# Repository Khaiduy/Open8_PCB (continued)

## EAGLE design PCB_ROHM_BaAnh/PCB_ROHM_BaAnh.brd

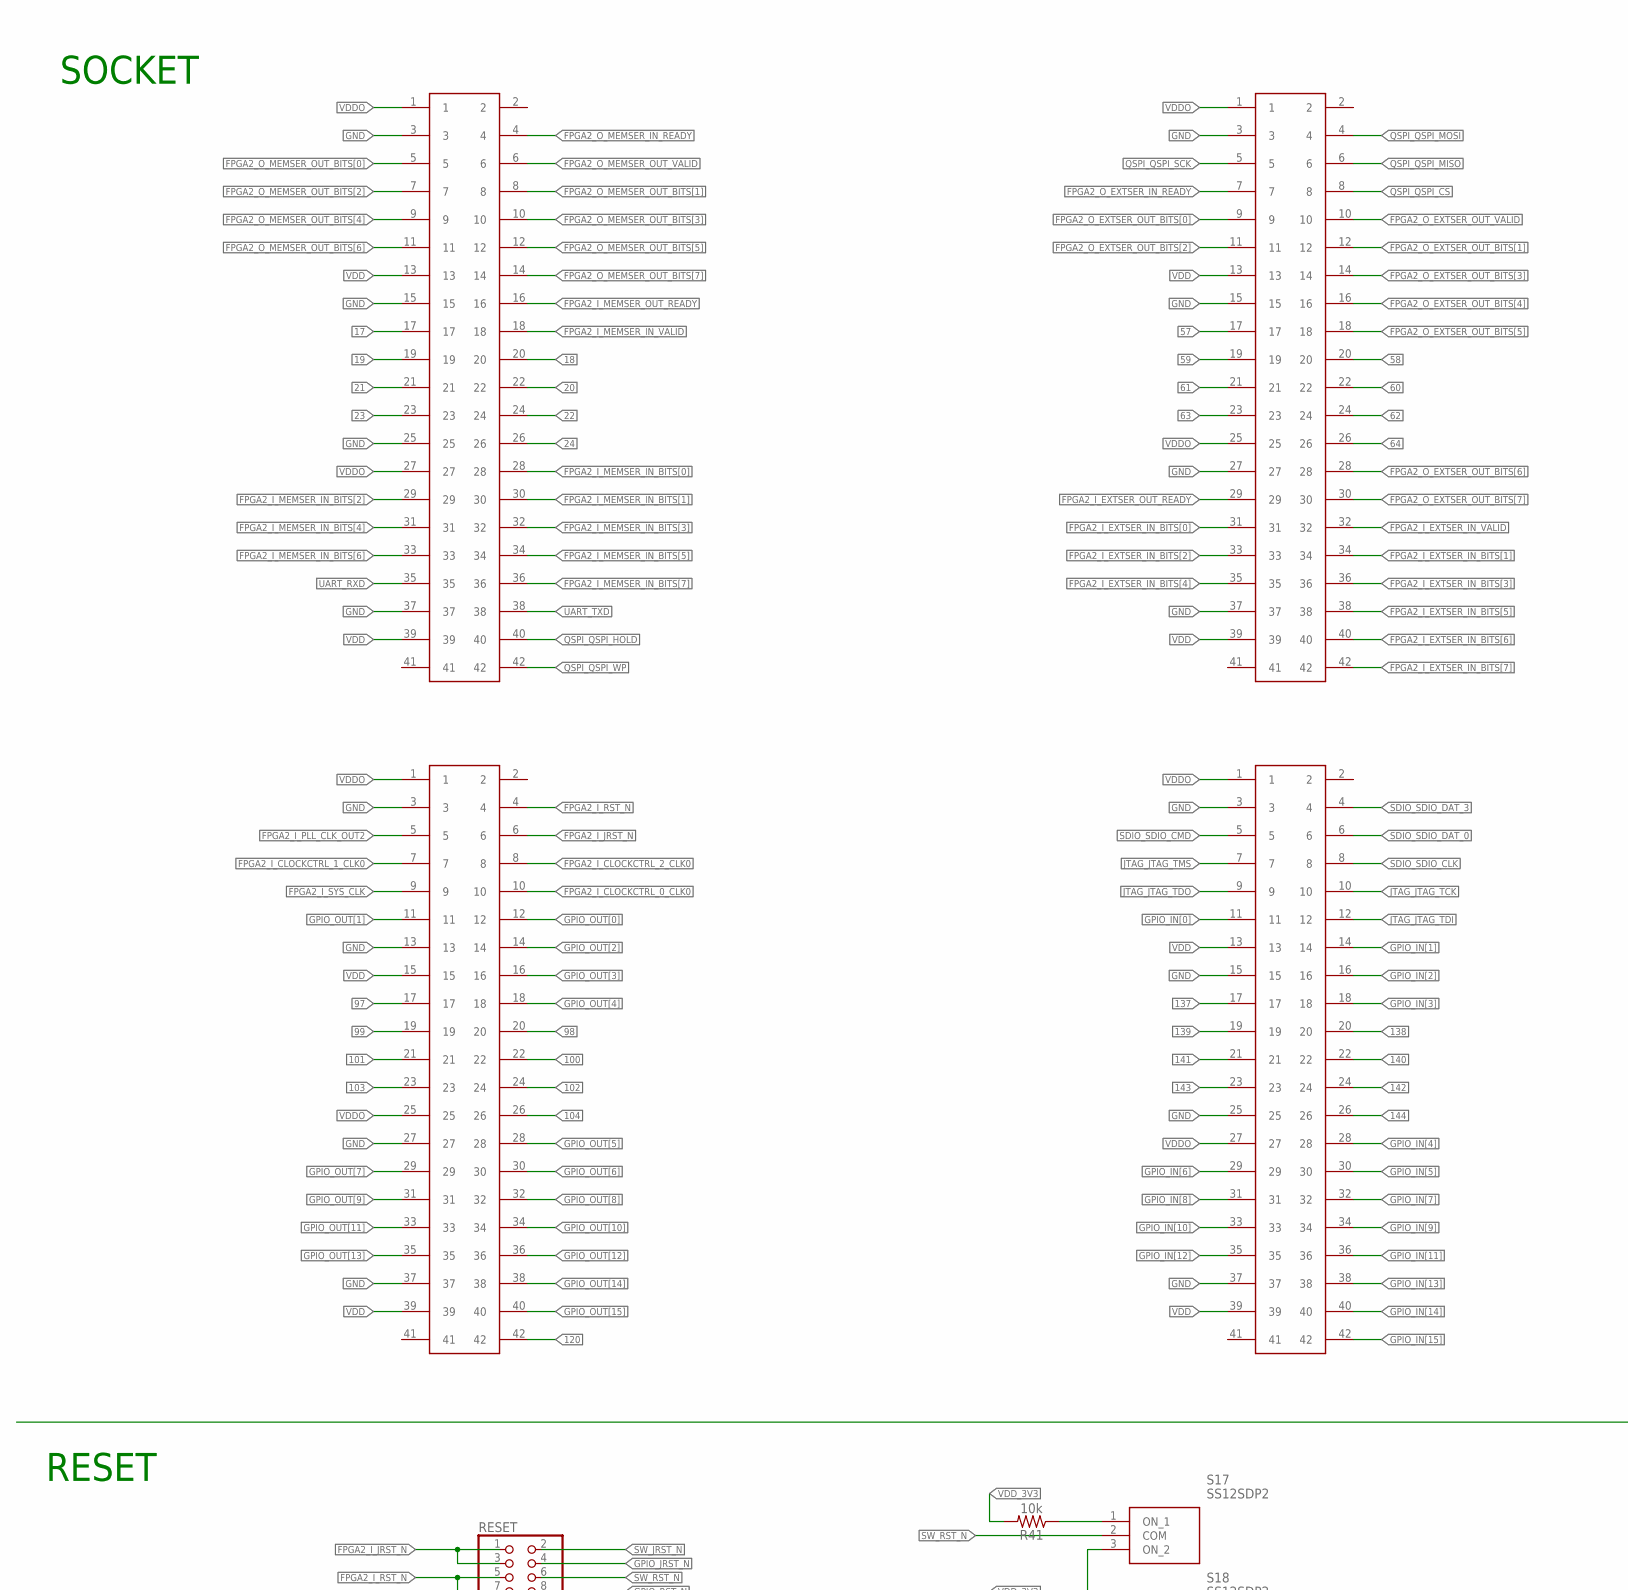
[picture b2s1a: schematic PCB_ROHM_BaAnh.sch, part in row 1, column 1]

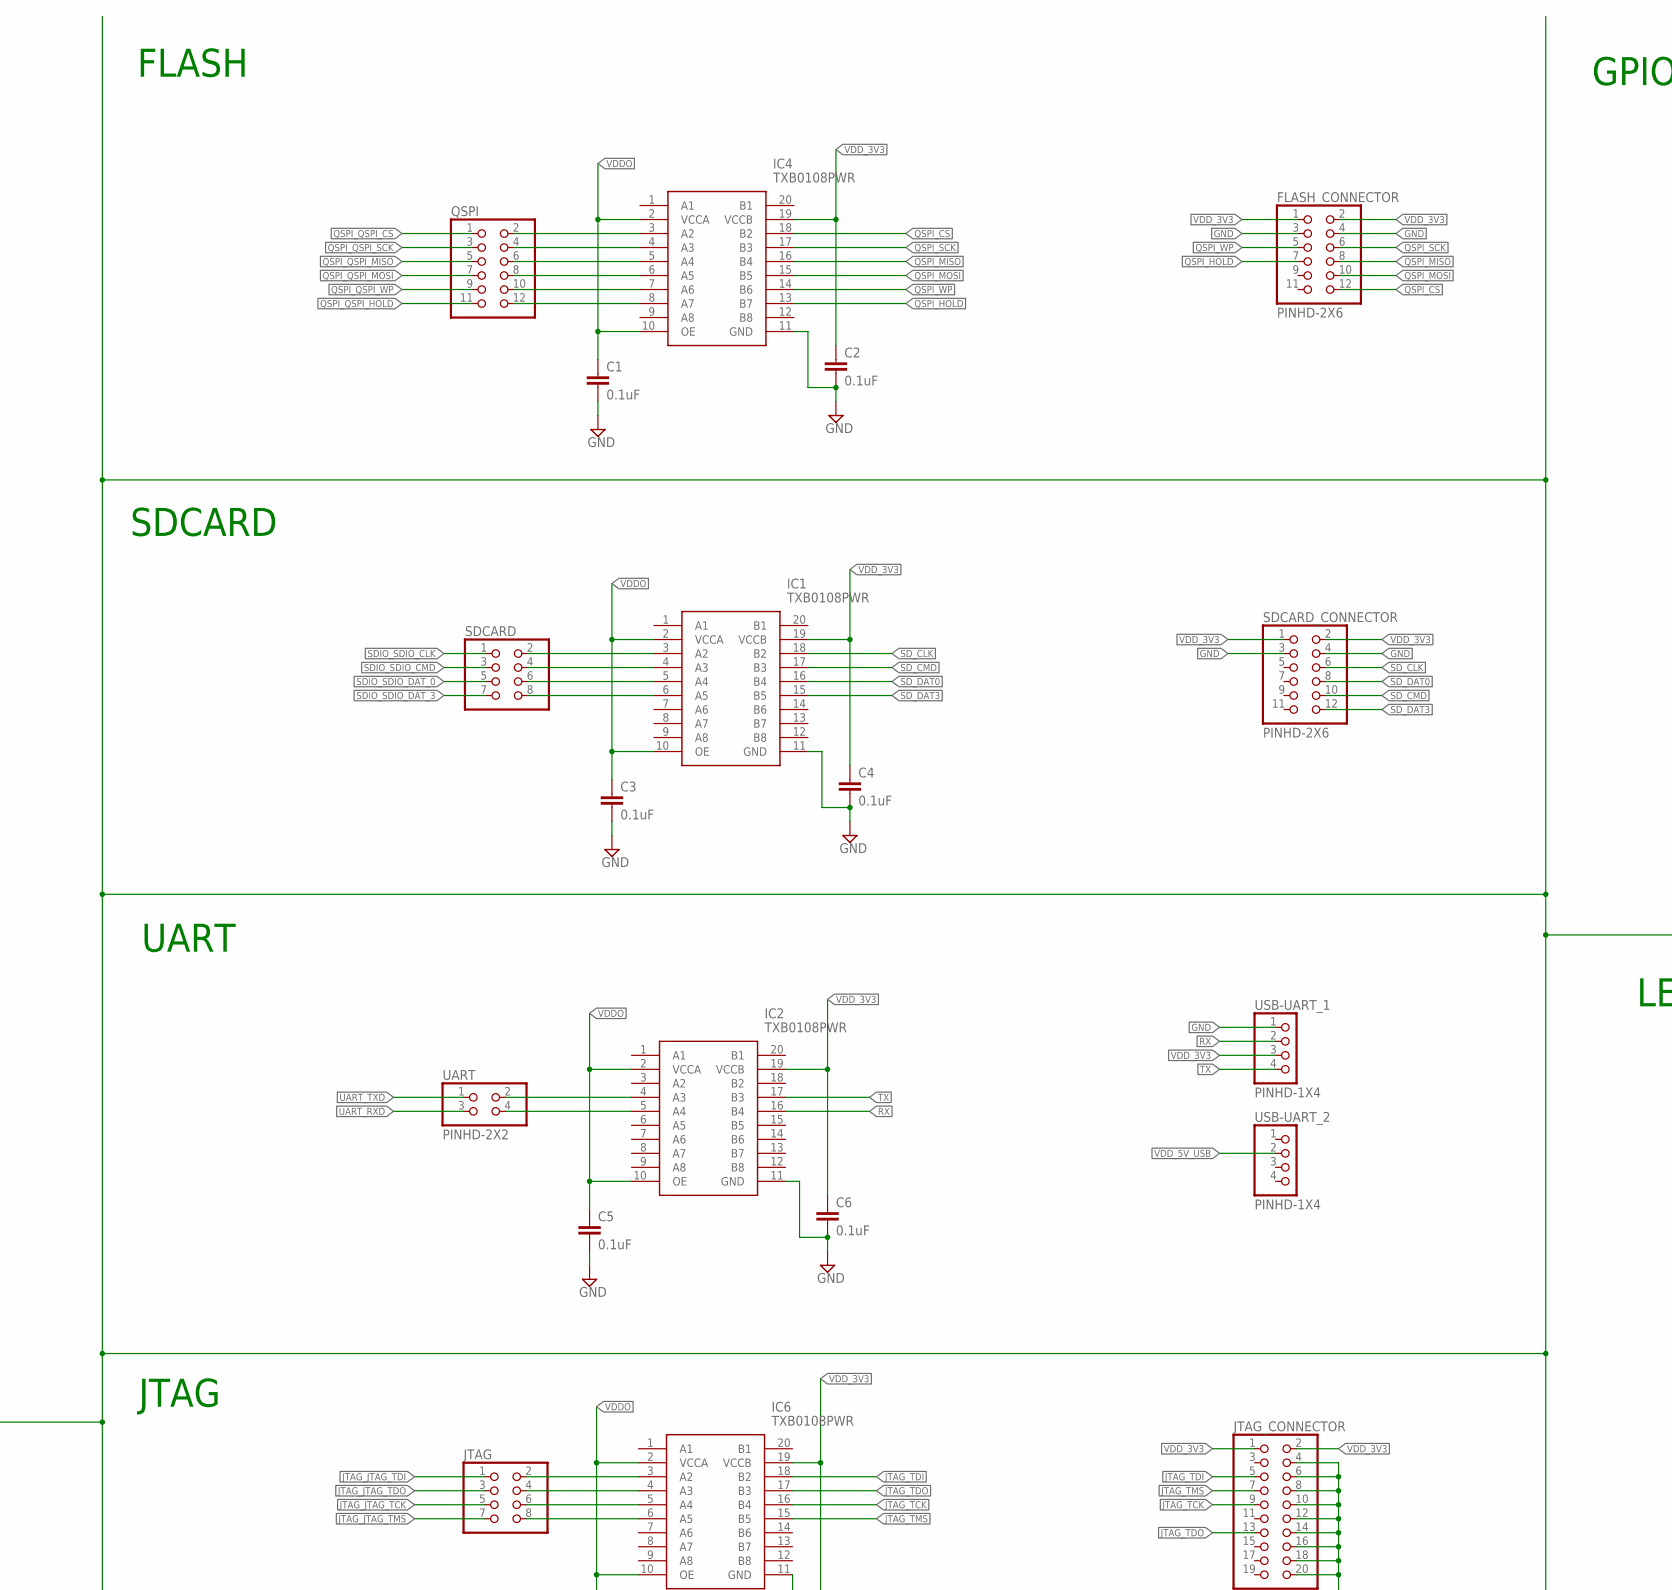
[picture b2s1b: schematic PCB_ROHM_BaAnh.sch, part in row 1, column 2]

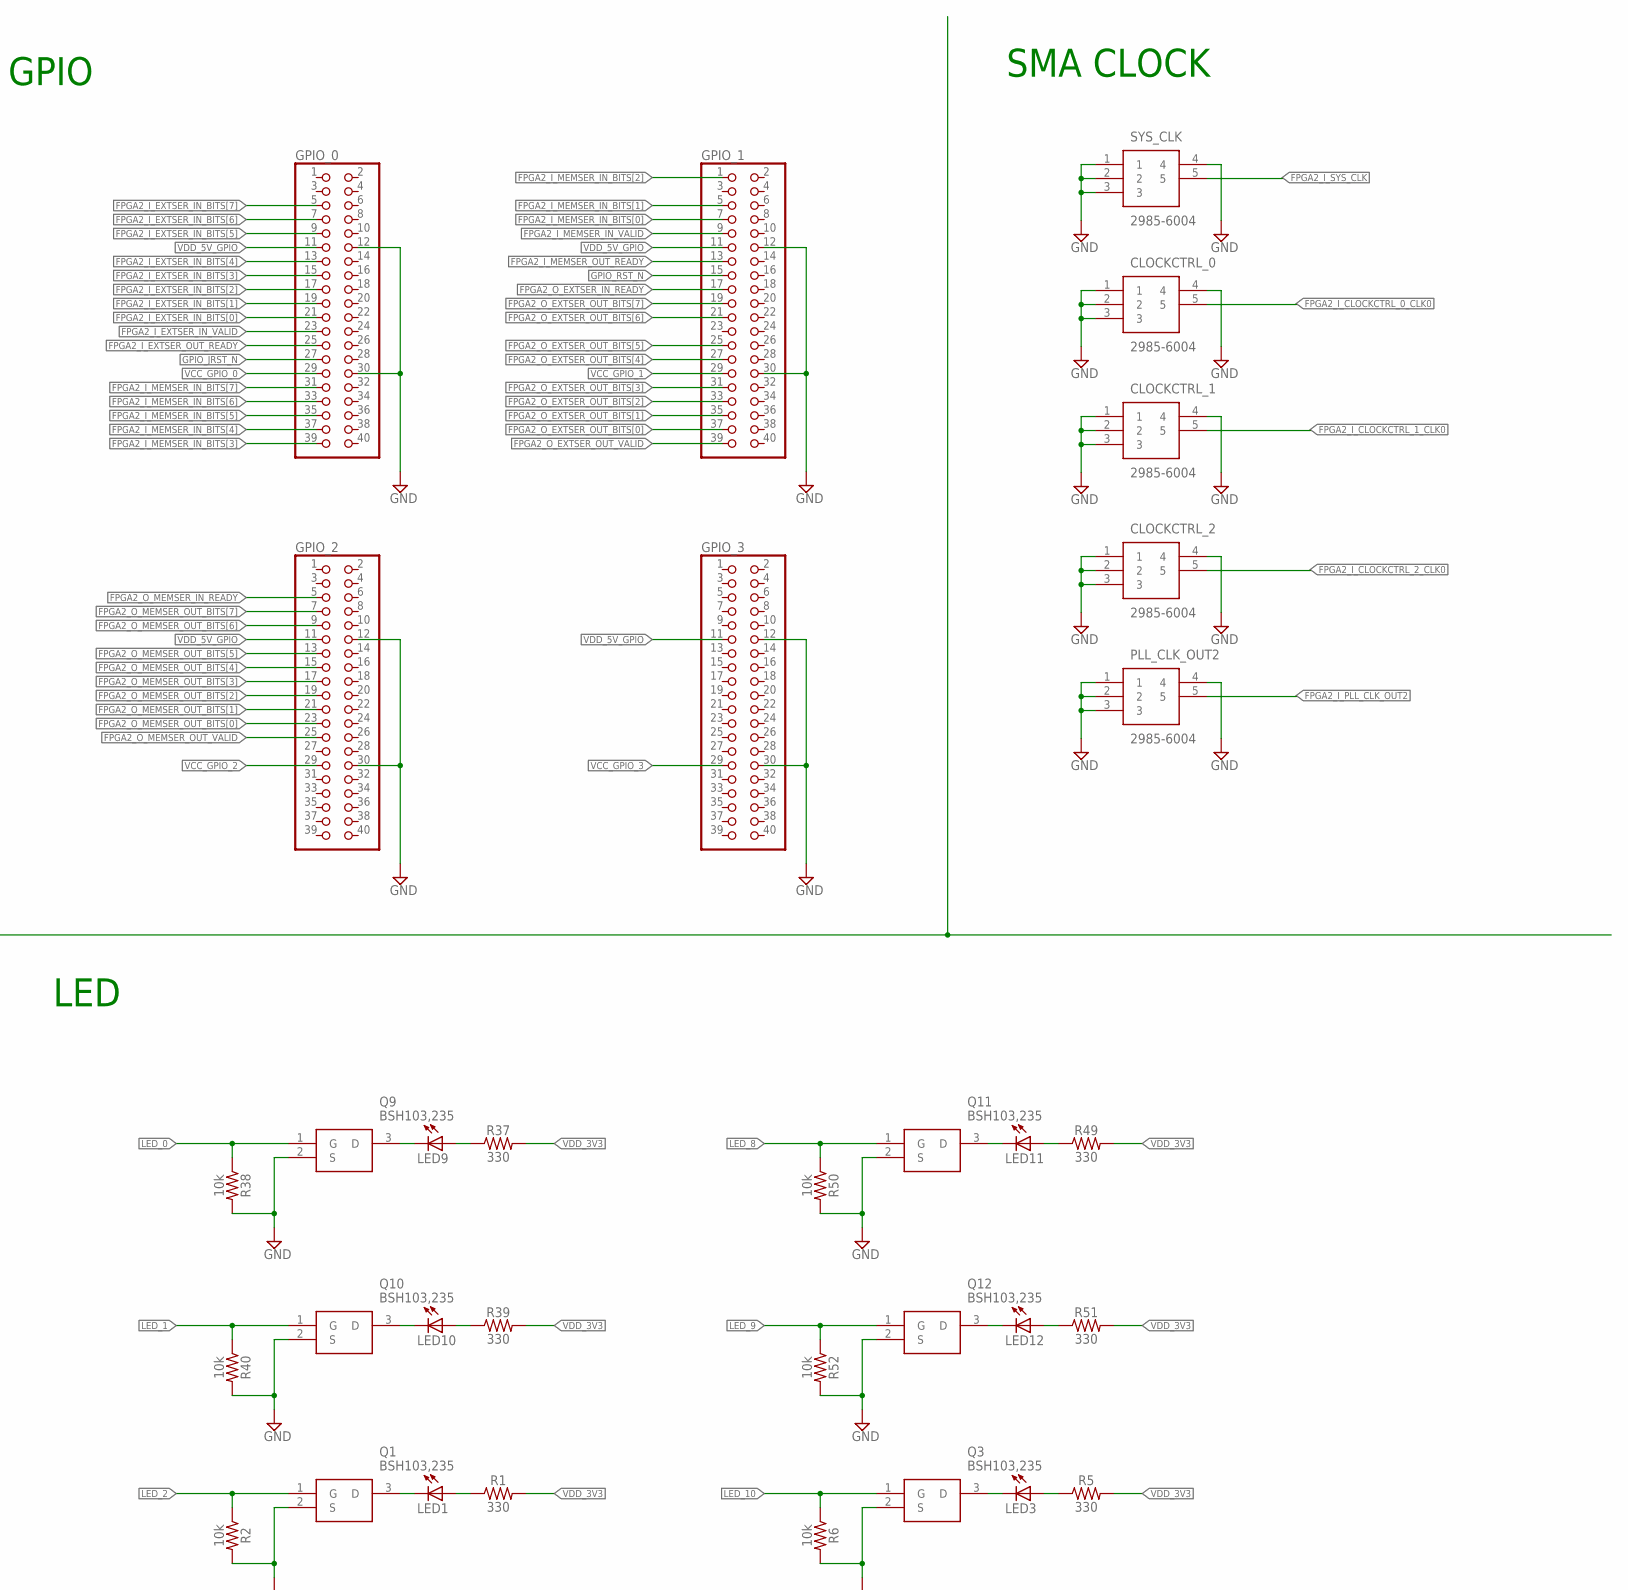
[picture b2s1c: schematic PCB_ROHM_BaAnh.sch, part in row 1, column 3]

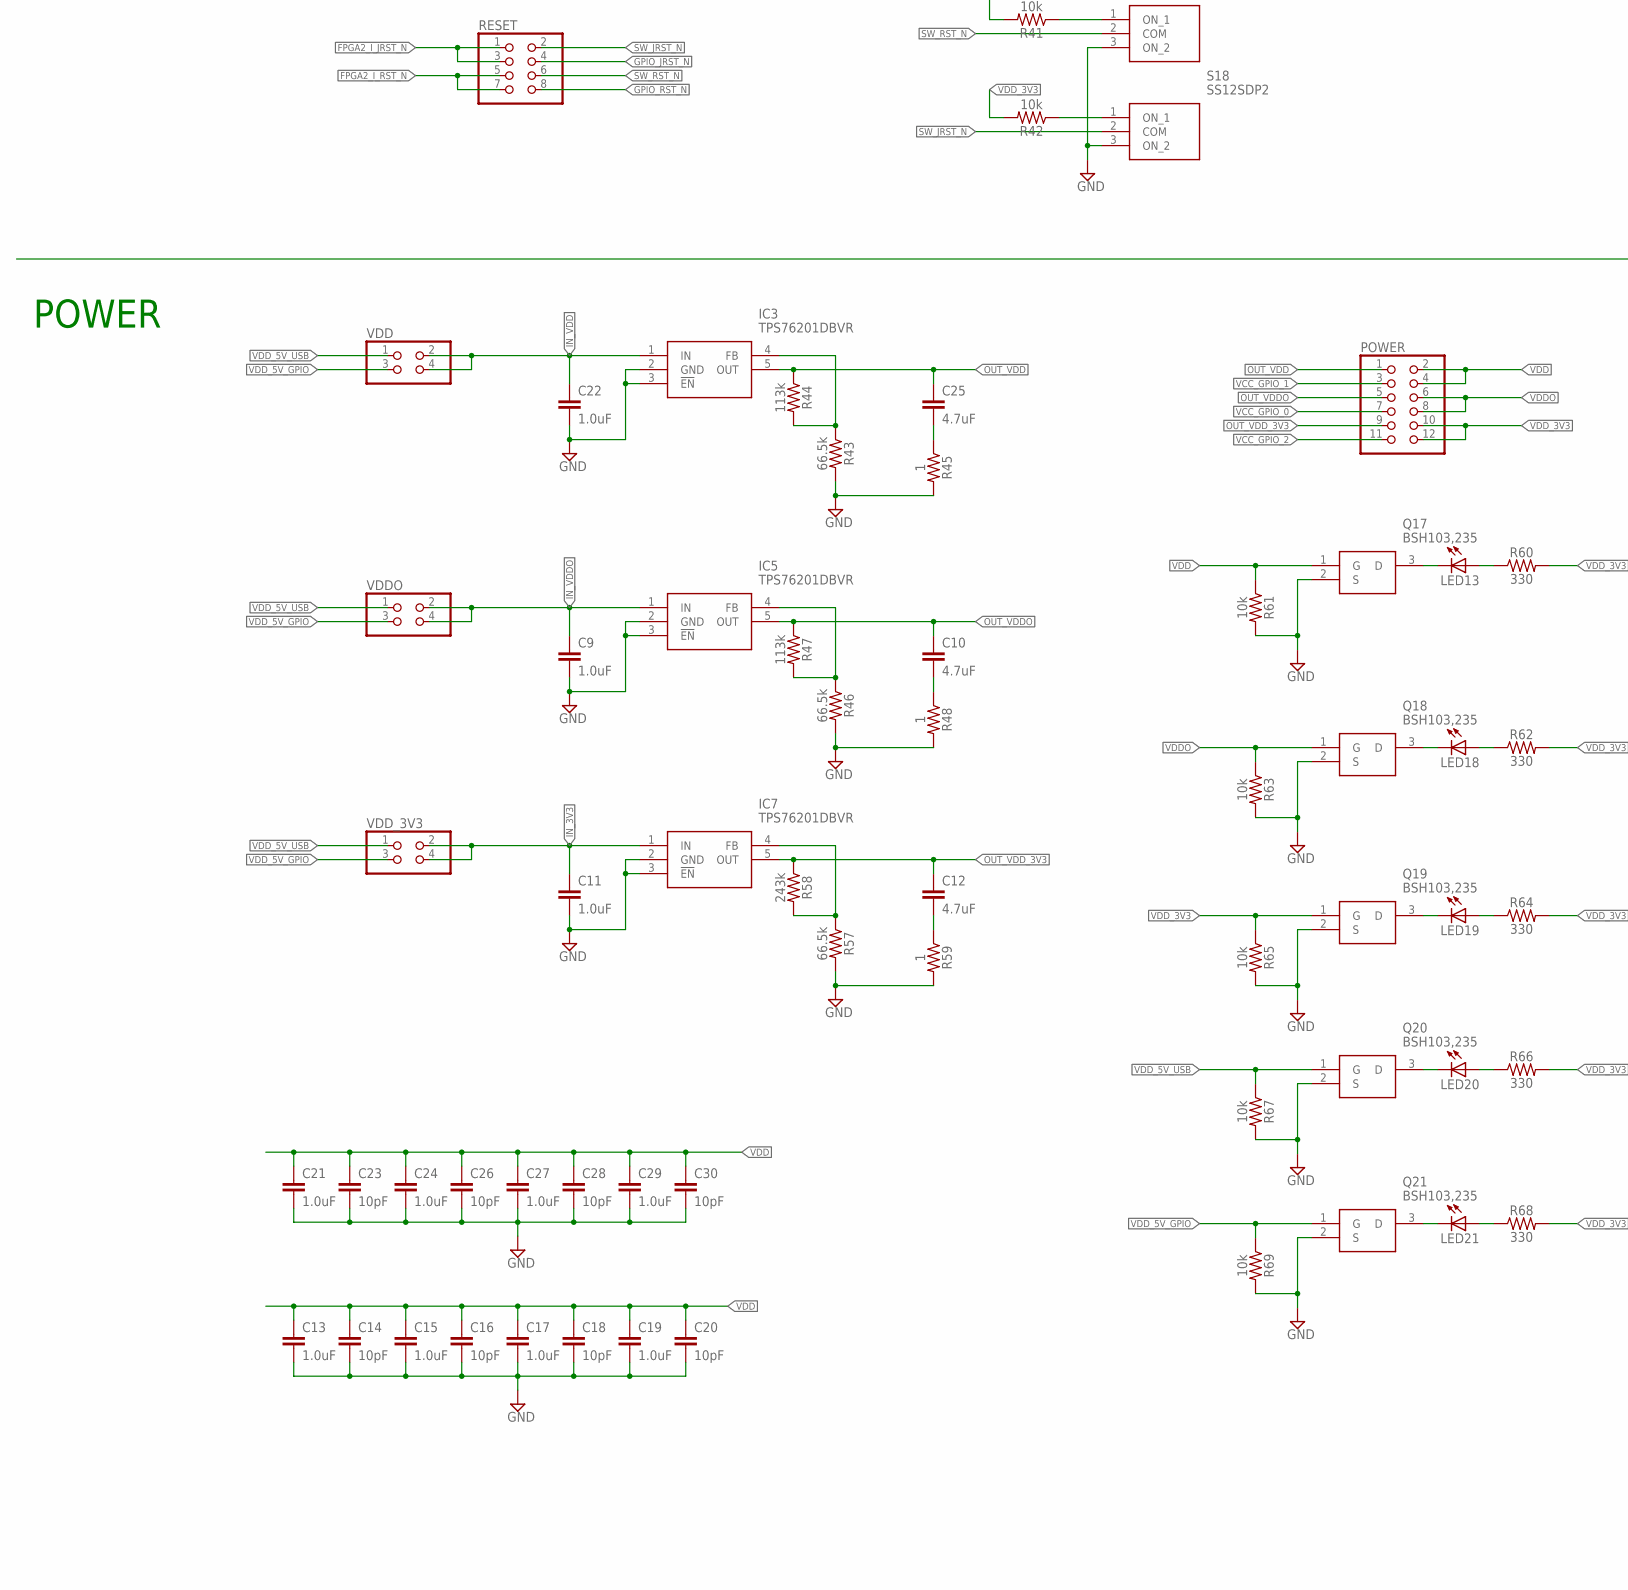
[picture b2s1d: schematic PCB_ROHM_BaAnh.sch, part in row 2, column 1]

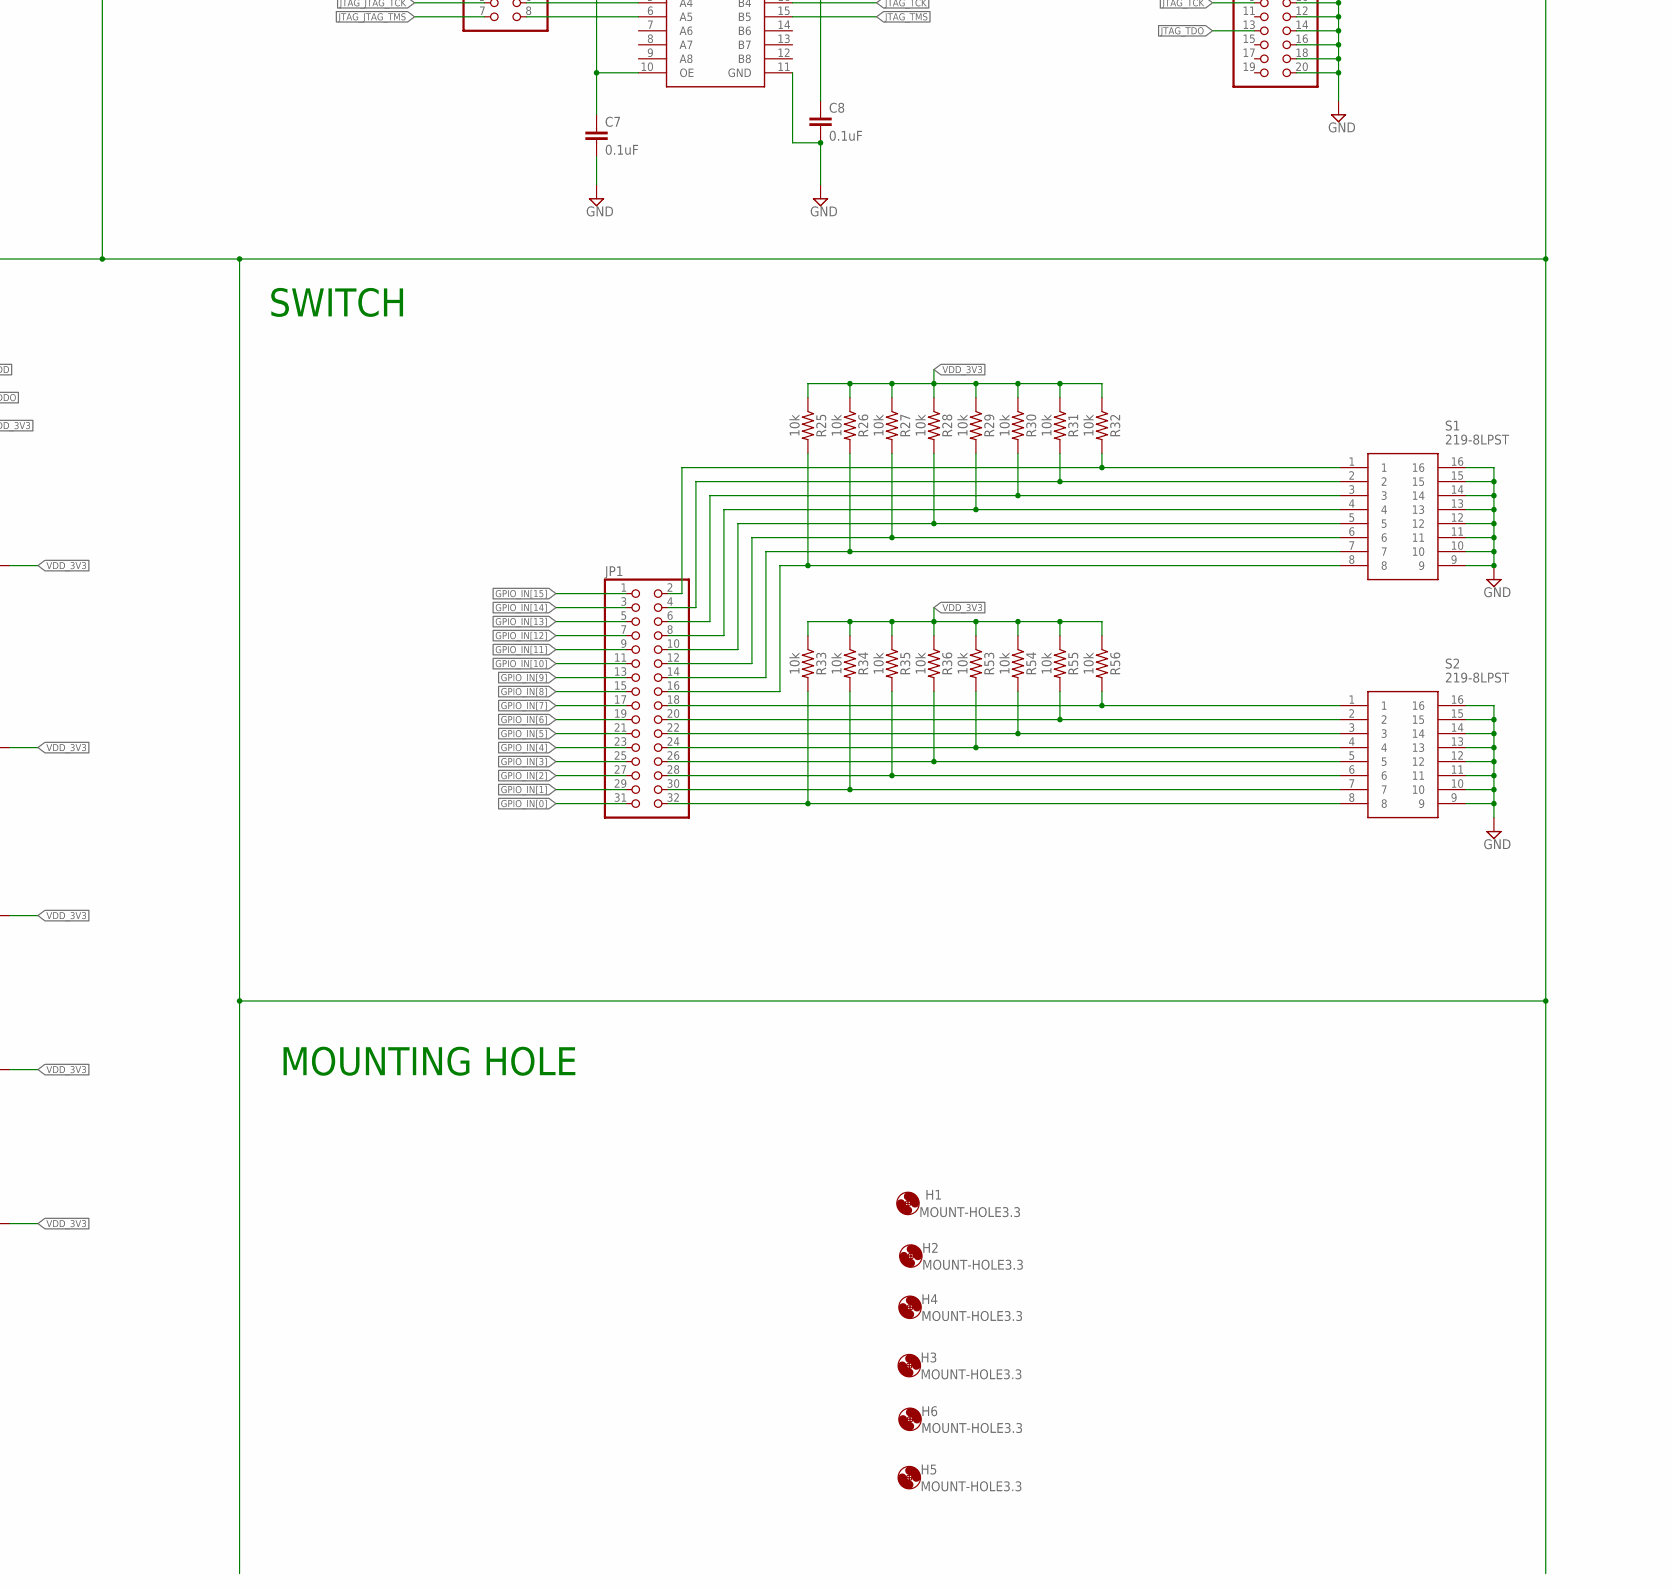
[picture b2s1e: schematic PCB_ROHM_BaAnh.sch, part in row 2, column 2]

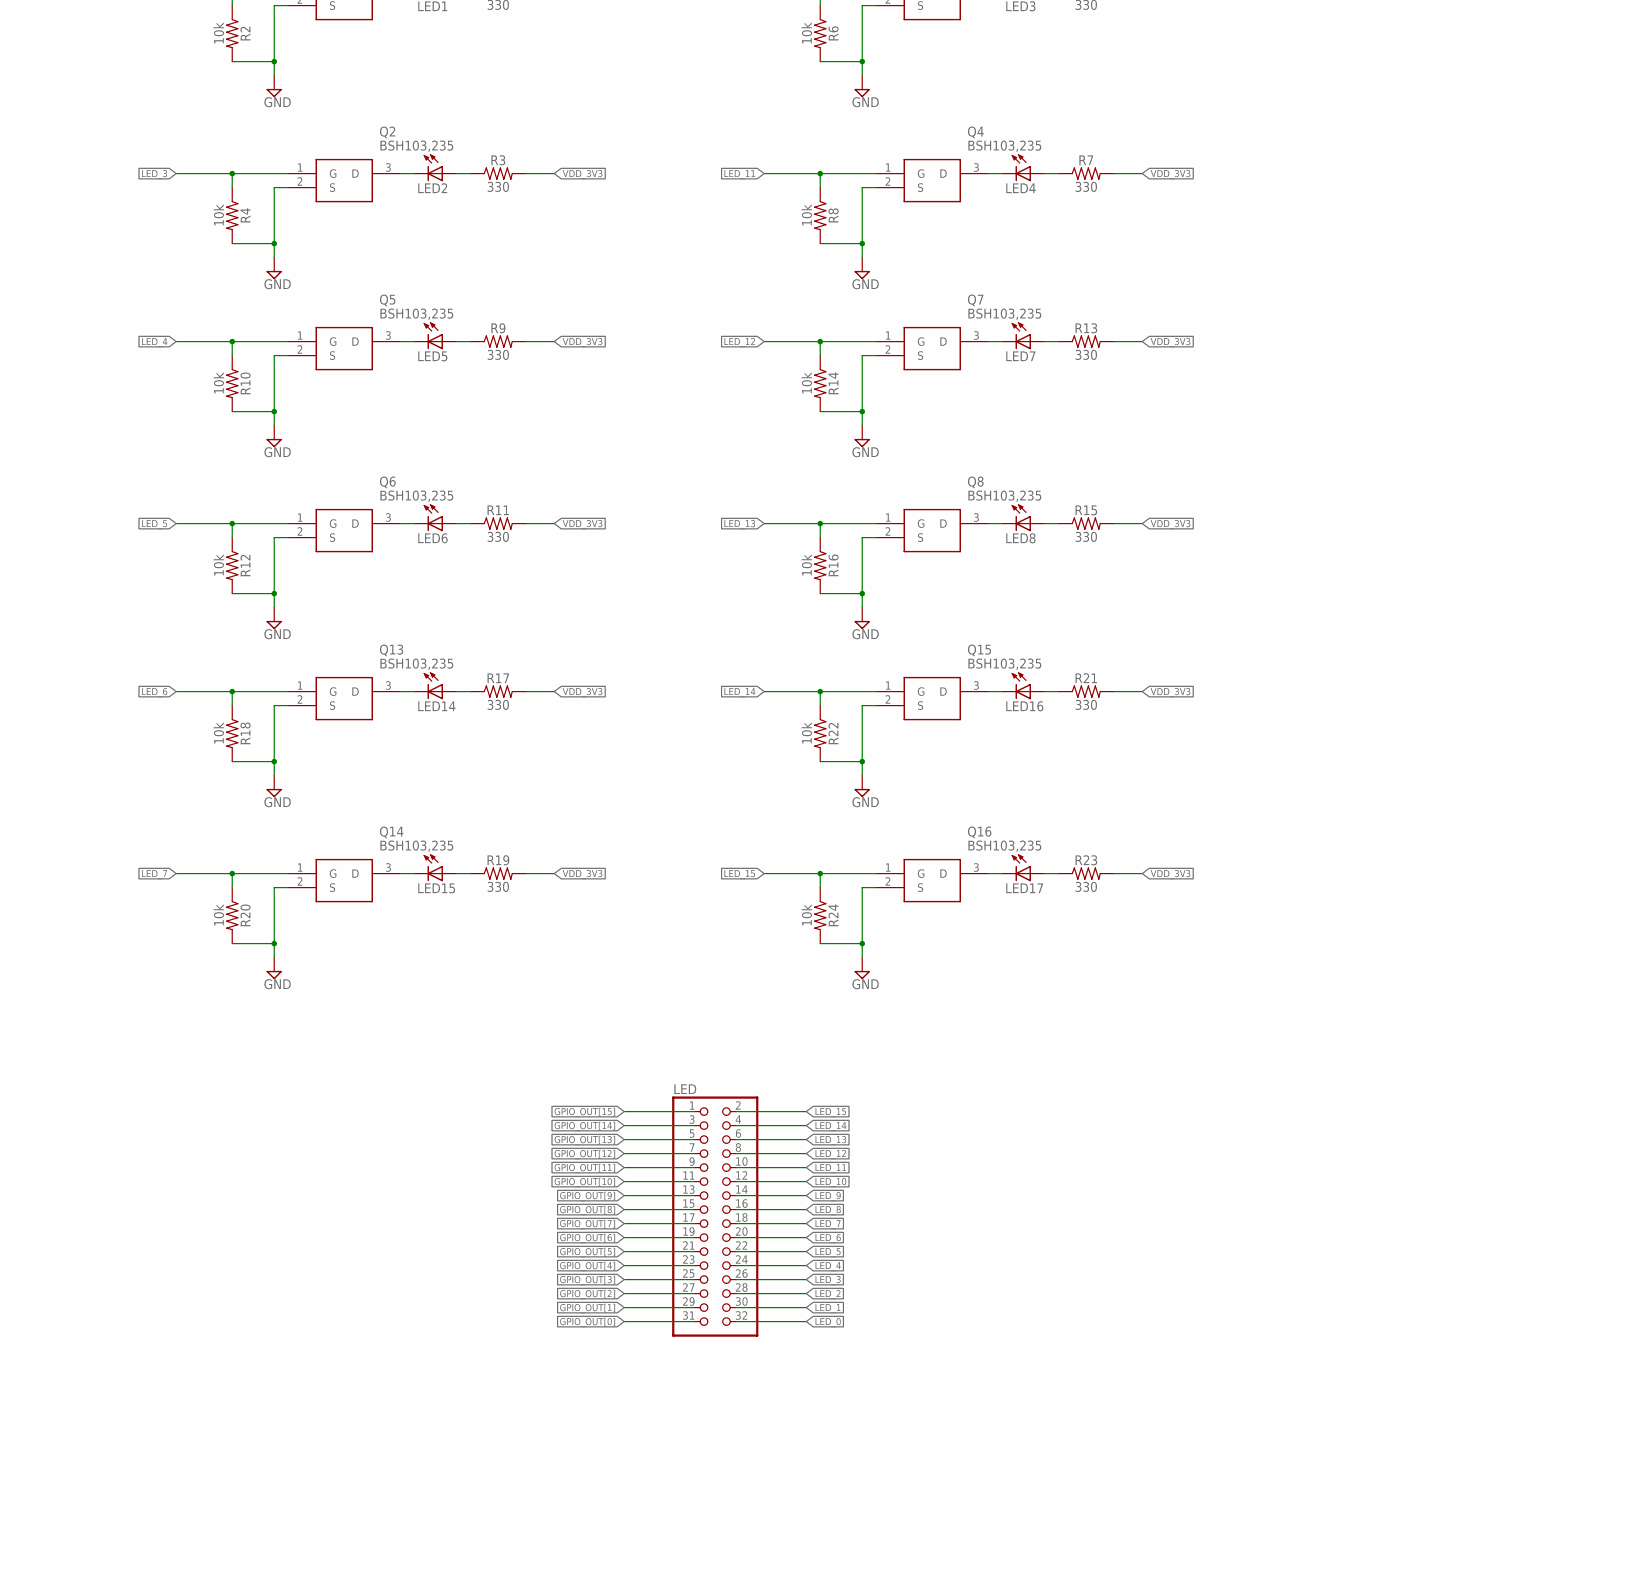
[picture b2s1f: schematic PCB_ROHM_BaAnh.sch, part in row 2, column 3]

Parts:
C1, C2, C3, C4, C5, C6, C7, C8: 0.1uF; 0805
C9, C11, C13, C15, C17, C19, C21, C22, C24, C27, C29: 1.0uF; 0805
C10, C12, C25: 4.7uF; 0805
C14, C16, C18, C20, C23, C26, C28, C30: 10pF; 0805
CLOCKCTRL_0, CLOCKCTRL_1, CLOCKCTRL_2: 2985-6004; 29856004
FLASH_CONNECTOR: PINHD-2X6; 2X06
GPIO_0, GPIO_1, GPIO_2, GPIO_3: PINHD-2X20; 2X20
H1, H2, H3, H4, H5, H6: MOUNT-HOLE3.3; 3,3
IC1, IC2, IC4, IC6: TXB0108PWR; SOP65P640X120-20N
IC3, IC5, IC7: TPS76201DBVR; SOT95P280X145-5N
JP1: PINHD-2X16; 2X16
JTAG: PINHD-2X4; 2X04
JTAG_CONNECTOR: PINHD-2X10; 2X10
LED: PINHD-2X16; 2X16
LED1, LED2, LED3, LED4, LED5, LED6, LED7, LED8, LED9, LED10, LED11, LED12, LED13, LED14, LED15, LED16, LED17, LED18, LED19, LED20, LED21: LEDCHIP-LED0805; CHIP-LED0805
PLL_CLK_OUT2: 2985-6004; 29856004
POWER: PINHD-2X6; 2X06
Q1, Q2, Q3, Q4, Q5, Q6, Q7, Q8, Q9, Q10, Q11, Q12, Q13, Q14, Q15, Q16, Q17, Q18, Q19, Q20, Q21: BSH103,235; SOT95P230X110-3N
QSPI: PINHD-2X6; 2X06
R1, R3, R5, R7, R9, R11, R13, R15, R17, R19, R21, R23, R37, R39, R49, R51, R60, R62, R64, R66, R68: 330; 0805
R2, R4, R6, R8, R10, R12, R14, R16, R18, R20, R22, R24, R25, R26, R27, R28, R29, R30, R31, R32, R33, R34, R35, R36, R38, R40, R41, R42, R50, R52, R53, R54, R55, R56, R61, R63, R65, R67, R69: 10k; 0805
R43, R46, R57: 66.5k; 0805
R44, R47: 113k; 0805
R45, R48, R59: 1; 0805
R58: 243k; 0805
RESET: PINHD-2X4; 2X04
S1, S2: 219-8LPST; 2198LPST
S17, S18: SS12SDP2
SDCARD: PINHD-2X4; 2X04
SDCARD_CONNECTOR: PINHD-2X6; 2X06
SYS_CLK: 2985-6004; 29856004
U$1, U$2, U$3, U$4: 2X41_HEADER
UART: PINHD-2X2; 2X02
USB-UART_1, USB-UART_2: PINHD-1X4; 1X04
VDD: PINHD-2X2; 2X02
VDDO: PINHD-2X2; 2X02
VDD_3V3: PINHD-2X2; 2X02

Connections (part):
17: U$1.17
18: U$1.20
19: U$1.19
20: U$1.22
21: U$1.21
22: U$1.24
23: U$1.23
24: U$1.26
57: U$2.17
58: U$2.20
59: U$2.19
60: U$2.22
61: U$2.21
62: U$2.24
63: U$2.23
64: U$2.26
97: U$3.17
98: U$3.20
99: U$3.19
100: U$3.22
101: U$3.21
102: U$3.24
103: U$3.23
104: U$3.26
120: U$3.42
137: U$4.17
138: U$4.20
139: U$4.19
140: U$4.22
141: U$4.21
142: U$4.24
143: U$4.23
144: U$4.26
FPGA2_I_CLOCKCTRL_0_CLK0: CLOCKCTRL_0.5, U$3.10
FPGA2_I_CLOCKCTRL_1_CLK0: CLOCKCTRL_1.5, U$3.7
FPGA2_I_CLOCKCTRL_2_CLK0: CLOCKCTRL_2.5, U$3.8
FPGA2_I_EXTSER_IN_BITS[0]: GPIO_0.21, U$2.31
FPGA2_I_EXTSER_IN_BITS[1]: GPIO_0.19, U$2.34
FPGA2_I_EXTSER_IN_BITS[2]: GPIO_0.17, U$2.33
FPGA2_I_EXTSER_IN_BITS[3]: GPIO_0.15, U$2.36
FPGA2_I_EXTSER_IN_BITS[4]: GPIO_0.13, U$2.35
FPGA2_I_EXTSER_IN_BITS[5]: GPIO_0.9, U$2.38
FPGA2_I_EXTSER_IN_BITS[6]: GPIO_0.7, U$2.40
FPGA2_I_EXTSER_IN_BITS[7]: GPIO_0.5, U$2.42
FPGA2_I_EXTSER_IN_VALID: GPIO_0.23, U$2.32
FPGA2_I_EXTSER_OUT_READY: GPIO_0.25, U$2.29
FPGA2_I_JRST_N: RESET.1, RESET.3, U$3.6
FPGA2_I_MEMSER_IN_BITS[0]: GPIO_1.7, U$1.28
FPGA2_I_MEMSER_IN_BITS[1]: GPIO_1.5, U$1.30
FPGA2_I_MEMSER_IN_BITS[2]: GPIO_1.1, U$1.29
FPGA2_I_MEMSER_IN_BITS[3]: GPIO_0.39, U$1.32
FPGA2_I_MEMSER_IN_BITS[4]: GPIO_0.37, U$1.31
FPGA2_I_MEMSER_IN_BITS[5]: GPIO_0.35, U$1.34
FPGA2_I_MEMSER_IN_BITS[6]: GPIO_0.33, U$1.33
FPGA2_I_MEMSER_IN_BITS[7]: GPIO_0.31, U$1.36
FPGA2_I_MEMSER_IN_VALID: GPIO_1.9, U$1.18
FPGA2_I_MEMSER_OUT_READY: GPIO_1.13, U$1.16
FPGA2_I_PLL_CLK_OUT2: PLL_CLK_OUT2.5, U$3.5
FPGA2_I_RST_N: RESET.5, RESET.7, U$3.4
FPGA2_I_SYS_CLK: SYS_CLK.5, U$3.9
FPGA2_O_EXTSER_IN_READY: GPIO_1.17, U$2.7
FPGA2_O_EXTSER_OUT_BITS[0]: GPIO_1.37, U$2.9
FPGA2_O_EXTSER_OUT_BITS[1]: GPIO_1.35, U$2.12
FPGA2_O_EXTSER_OUT_BITS[2]: GPIO_1.33, U$2.11
FPGA2_O_EXTSER_OUT_BITS[3]: GPIO_1.31, U$2.14
FPGA2_O_EXTSER_OUT_BITS[4]: GPIO_1.27, U$2.16
FPGA2_O_EXTSER_OUT_BITS[5]: GPIO_1.25, U$2.18
FPGA2_O_EXTSER_OUT_BITS[6]: GPIO_1.21, U$2.28
FPGA2_O_EXTSER_OUT_BITS[7]: GPIO_1.19, U$2.30
FPGA2_O_EXTSER_OUT_VALID: GPIO_1.39, U$2.10
FPGA2_O_MEMSER_IN_READY: GPIO_2.5, U$1.4
FPGA2_O_MEMSER_OUT_BITS[0]: GPIO_2.23, U$1.5
FPGA2_O_MEMSER_OUT_BITS[1]: GPIO_2.21, U$1.8
FPGA2_O_MEMSER_OUT_BITS[2]: GPIO_2.19, U$1.7
FPGA2_O_MEMSER_OUT_BITS[3]: GPIO_2.17, U$1.10
FPGA2_O_MEMSER_OUT_BITS[4]: GPIO_2.15, U$1.9
FPGA2_O_MEMSER_OUT_BITS[5]: GPIO_2.13, U$1.12
FPGA2_O_MEMSER_OUT_BITS[6]: GPIO_2.9, U$1.11
FPGA2_O_MEMSER_OUT_BITS[7]: GPIO_2.7, U$1.14
FPGA2_O_MEMSER_OUT_VALID: GPIO_2.25, U$1.6
GND: C1.2, C2.2, C3.2, C4.2, C5.2, C6.2, C7.2, C8.2, C9.2, C11.2, C13.2, C14.2, C15.2, C16.2, C17.2, C18.2, C19.2, C20.2, C21.2, C22.2, C23.2, C24.2, C26.2, C27.2, C28.2, C29.2, C30.2, CLOCKCTRL_0.1, CLOCKCTRL_0.2, CLOCKCTRL_0.3, CLOCKCTRL_0.4, CLOCKCTRL_1.1, CLOCKCTRL_1.2, CLOCKCTRL_1.3, CLOCKCTRL_1.4, CLOCKCTRL_2.1, CLOCKCTRL_2.2, CLOCKCTRL_2.3, CLOCKCTRL_2.4, FLASH_CONNECTOR.3, FLASH_CONNECTOR.4, GPIO_0.12, GPIO_0.30, GPIO_1.12, GPIO_1.30, GPIO_2.12, GPIO_2.30, GPIO_3.12, GPIO_3.30, IC1.11 (GND), IC2.11 (GND), IC3.2 (GND), IC3.3 (!EN), IC4.11 (GND), IC5.2 (GND), IC5.3 (!EN), IC6.11 (GND), IC7.2 (GND), IC7.3 (!EN), JTAG_CONNECTOR.4, JTAG_CONNECTOR.6, JTAG_CONNECTOR.8, JTAG_CONNECTOR.10, JTAG_CONNECTOR.12, JTAG_CONNECTOR.14, JTAG_CONNECTOR.16, JTAG_CONNECTOR.18, JTAG_CONNECTOR.20, PLL_CLK_OUT2.1, PLL_CLK_OUT2.2, PLL_CLK_OUT2.3, PLL_CLK_OUT2.4, Q1.2 (S), Q2.2 (S), Q3.2 (S), Q4.2 (S), Q5.2 (S), Q6.2 (S), Q7.2 (S), Q8.2 (S)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
GPIO_IN[0]: JP1.31, U$4.11
GPIO_IN[1]: JP1.29, U$4.14
GPIO_IN[2]: JP1.27, U$4.16
GPIO_IN[3]: JP1.25, U$4.18
GPIO_IN[4]: JP1.23, U$4.28
GPIO_IN[5]: JP1.21, U$4.30
GPIO_IN[6]: JP1.19, U$4.29
GPIO_IN[7]: JP1.17, U$4.32
GPIO_IN[8]: JP1.15, U$4.31
GPIO_IN[9]: JP1.13, U$4.34
GPIO_IN[10]: JP1.11, U$4.33
GPIO_IN[11]: JP1.9, U$4.36
GPIO_IN[12]: JP1.7, U$4.35
GPIO_IN[13]: JP1.5, U$4.38
GPIO_IN[14]: JP1.3, U$4.40
GPIO_IN[15]: JP1.1, U$4.42
GPIO_JRST_N: GPIO_0.27, RESET.4
GPIO_OUT[0]: LED.31, U$3.12
GPIO_OUT[1]: LED.29, U$3.11
GPIO_OUT[2]: LED.27, U$3.14
GPIO_OUT[3]: LED.25, U$3.16
GPIO_OUT[4]: LED.23, U$3.18
GPIO_OUT[5]: LED.21, U$3.28
GPIO_OUT[6]: LED.19, U$3.30
GPIO_OUT[7]: LED.17, U$3.29
GPIO_OUT[8]: LED.15, U$3.32
GPIO_OUT[9]: LED.13, U$3.31
GPIO_OUT[10]: LED.11, U$3.34
GPIO_OUT[11]: LED.9, U$3.33
GPIO_OUT[12]: LED.7, U$3.36
GPIO_OUT[13]: LED.5, U$3.35
GPIO_OUT[14]: LED.3, U$3.38
GPIO_OUT[15]: LED.1, U$3.40
GPIO_RST_N: GPIO_1.15, RESET.8
IN_3V3: C11.1, IC7.1 (IN), VDD_3V3.2, VDD_3V3.4
IN_VDD: C22.1, IC3.1 (IN), VDD.2, VDD.4
IN_VDDO: C9.1, IC5.1 (IN), VDDO.2, VDDO.4
JTAG_JTAG_TCK: JTAG.5, U$4.10
JTAG_JTAG_TDI: JTAG.1, U$4.12
JTAG_JTAG_TDO: JTAG.3, U$4.9
JTAG_JTAG_TMS: JTAG.7, U$4.7
JTAG_TCK: IC6.16 (B4), JTAG_CONNECTOR.9
JTAG_TDI: IC6.18 (B2), JTAG_CONNECTOR.5
JTAG_TDO: IC6.17 (B3), JTAG_CONNECTOR.13
JTAG_TMS: IC6.15 (B5), JTAG_CONNECTOR.7
LED_0: LED.32, Q9.1 (G), R38.1
LED_1: LED.30, Q10.1 (G), R40.1
LED_2: LED.28, Q1.1 (G), R2.1
LED_3: LED.26, Q2.1 (G), R4.1
LED_4: LED.24, Q5.1 (G), R10.1
LED_5: LED.22, Q6.1 (G), R12.1
LED_6: LED.20, Q13.1 (G), R18.1
LED_7: LED.18, Q14.1 (G), R20.1
LED_8: LED.16, Q11.1 (G), R50.1
LED_9: LED.14, Q12.1 (G), R52.1
LED_10: LED.12, Q3.1 (G), R6.1
LED_11: LED.10, Q4.1 (G), R8.1
LED_12: LED.8, Q7.1 (G), R14.1
LED_13: LED.6, Q8.1 (G), R16.1
LED_14: LED.4, Q15.1 (G), R22.1
LED_15: LED.2, Q16.1 (G), R24.1
unnamed: IC1.3 (A2), SDCARD.2
unnamed: IC1.4 (A3), SDCARD.4
unnamed: IC1.5 (A4), SDCARD.6
unnamed: IC1.6 (A5), SDCARD.8
unnamed: IC6.3 (A2), JTAG.2
unnamed: IC2.4 (A3), UART.2
unnamed: IC2.5 (A4), UART.4
unnamed: IC6.4 (A3), JTAG.4
unnamed: IC6.5 (A4), JTAG.6
unnamed: IC6.6 (A5), JTAG.8
unnamed: R41.1, S17.1 (ON_1)
unnamed: LED1.C, Q1.3 (D)
unnamed: LED1.A, R1.1
unnamed: LED2.C, Q2.3 (D)
unnamed: LED9.C, Q9.3 (D)
unnamed: LED9.A, R37.1
unnamed: LED2.A, R3.1
unnamed: LED3.C, Q3.3 (D)
unnamed: LED3.A, R5.1
unnamed: LED4.C, Q4.3 (D)
unnamed: LED4.A, R7.1
unnamed: LED5.C, Q5.3 (D)
unnamed: LED5.A, R9.1
unnamed: LED6.C, Q6.3 (D)
unnamed: LED6.A, R11.1
unnamed: LED7.C, Q7.3 (D)
unnamed: LED7.A, R13.1
unnamed: LED8.C, Q8.3 (D)
unnamed: IC4.3 (A2), QSPI.2
unnamed: LED10.C, Q10.3 (D)
unnamed: LED8.A, R15.1
unnamed: LED14.C, Q13.3 (D)
unnamed: LED10.A, R39.1
unnamed: LED14.A, R17.1
unnamed: IC4.4 (A3), QSPI.4
unnamed: LED15.C, Q14.3 (D)
unnamed: IC4.5 (A4), QSPI.6
unnamed: IC4.6 (A5), QSPI.8
unnamed: LED15.A, R19.1
unnamed: LED16.C, Q15.3 (D)
unnamed: LED16.A, R21.1
unnamed: LED17.C, Q16.3 (D)
unnamed: LED17.A, R23.1
unnamed: R42.1, S18.1 (ON_1)
unnamed: IC3.4 (FB), R43.1, R44.2
unnamed: C25.2, R45.1
unnamed: IC5.4 (FB), R46.1, R47.2
unnamed: JP1.32, R33.2, S2.8
unnamed: JP1.30, R34.2, S2.7
unnamed: JP1.28, R35.2, S2.6
unnamed: JP1.26, R36.2, S2.5
unnamed: C10.2, R48.1
unnamed: IC7.4 (FB), R57.1, R58.2
unnamed: C12.2, R59.1
unnamed: LED13.C, Q17.3 (D)
unnamed: JP1.24, R53.2, S2.4
unnamed: JP1.22, R54.2, S2.3
unnamed: JP1.20, R55.2, S2.2
unnamed: LED11.C, Q11.3 (D)
unnamed: JP1.18, R56.2, S2.1
unnamed: LED11.A, R49.1
unnamed: LED13.A, R60.1
unnamed: LED12.C, Q12.3 (D)
unnamed: LED12.A, R51.1
unnamed: LED18.C, Q18.3 (D)
unnamed: JP1.16, R25.2, S1.8
unnamed: JP1.14, R26.2, S1.7
unnamed: JP1.12, R27.2, S1.6
unnamed: JP1.10, R28.2, S1.5
unnamed: LED18.A, R62.1
unnamed: LED19.C, Q19.3 (D)
unnamed: JP1.8, R29.2, S1.4
unnamed: JP1.6, R30.2, S1.3
unnamed: JP1.4, R31.2, S1.2
unnamed: JP1.2, R32.2, S1.1
unnamed: LED19.A, R64.1
unnamed: LED20.C, Q20.3 (D)
unnamed: LED20.A, R66.1
unnamed: LED21.C, Q21.3 (D)
unnamed: IC4.7 (A6), QSPI.10
unnamed: IC4.8 (A7), QSPI.12
unnamed: LED21.A, R68.1
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
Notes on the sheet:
SOCKET
RESET
POWER
SWITCH
JTAG
UART
SDCARD
FLASH
GPIO
SMA CLOCK
LED
MOUNTING HOLE

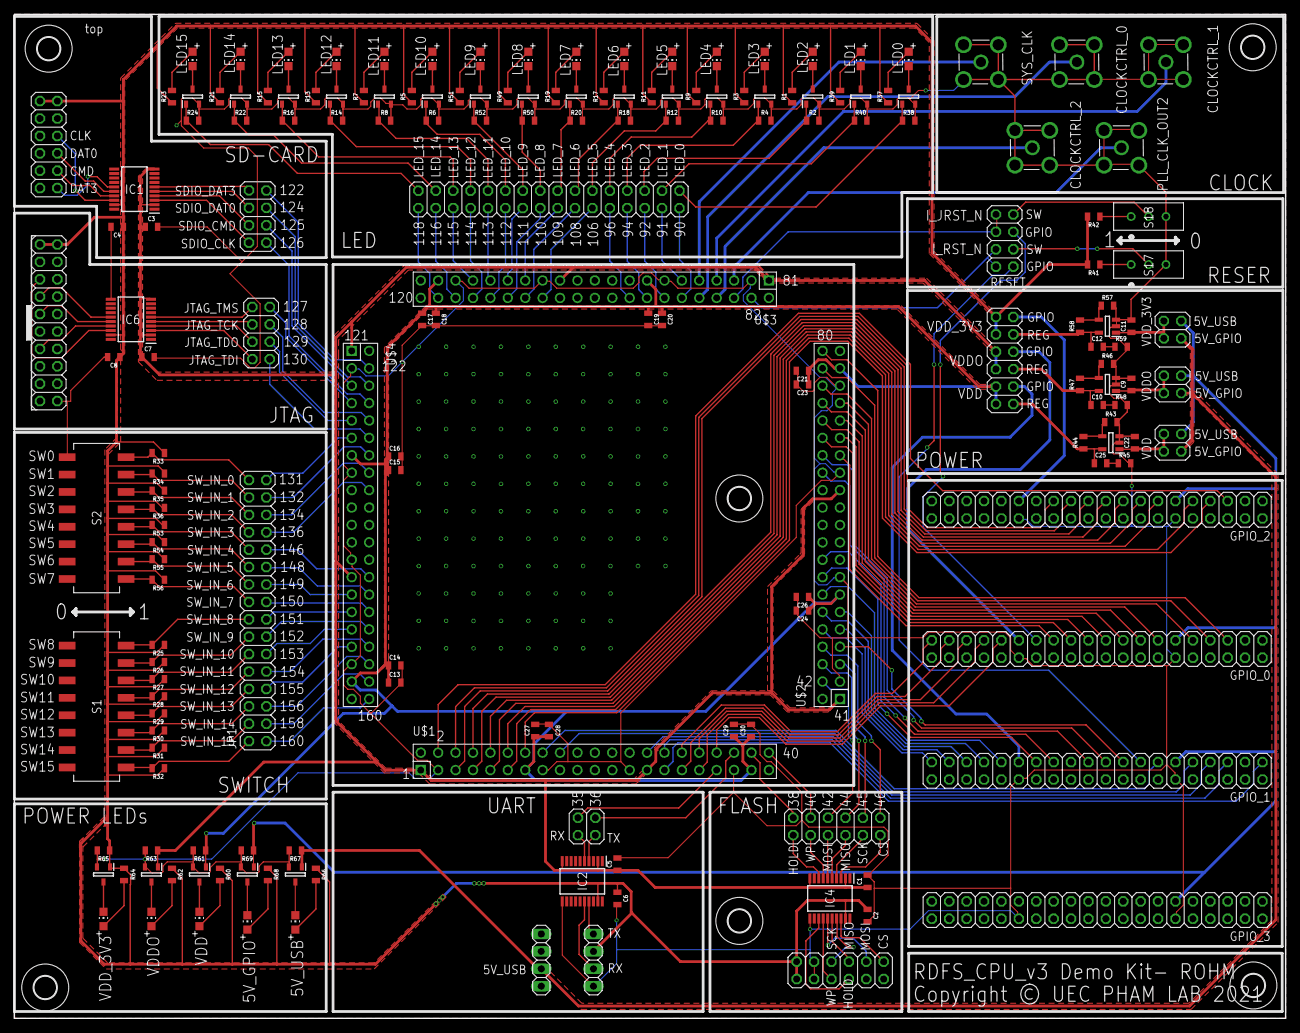
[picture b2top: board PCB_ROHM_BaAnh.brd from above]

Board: 2 copper layers, 185.5 x 146.5 mm, 187 parts (0 on the bottom side), 228 nets.

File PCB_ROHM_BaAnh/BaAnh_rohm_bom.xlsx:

Comment | Designator | Footprint | LCSC Part #（optional）
LED | LED1, LED2, LED3, LED4, LED5, LED6, LED7, LED8, LED9, LED10, LED11, LED12, LED1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 | 805 | C2290
0.1uF | C1, C2, C3, C4, C5, C6, C7, C8 | 805 | C476766
1ohm | R45, R48, R59 | 805 | C247113
1uF | C9, C11, C13, C15, C17, C19, C21, C22, C24, C27, C29 | 805 | C28323
10k | R2, R4, R6, R8, R10, R12, R14, R16, R18, R20, R22, R24, R25, R26, R27, R28, R29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 | 805 | C17414
10pF | C14, C16, C18, C20, C23, C26, C28, C30 | 805 | C1785
113k | R44, R47 | 805 | C17424
2198LPST | S1, S2 | 2198LPST | C314503
243k | R58 | 805 | C17573
330ohm | R1, R3, R5, R7, R9, R11, R13, R15, R17, R19, R21, R23, R37, R39, R49, R51, R60,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 | 805 | C17630
4.7uF | C10, C12, C25 | 805 | C98195
66.5k | R43, R46, R57 | 805 | C17791
BSH103,235 | Q1, Q2, Q3, Q4, Q5, Q6, Q7, Q8, Q9, Q10, Q11, Q12, Q13, Q14, Q15, Q16, Q17, Q18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 | SOT-23-3 | C88711
TPS76201DBVR | IC3, IC5, IC7 | SOT-23-5 | C13997
TXB0108PWR | IC1, IC2, IC4, IC6 | TSSOP-20_4.4x6.5x0.65P | C53406
